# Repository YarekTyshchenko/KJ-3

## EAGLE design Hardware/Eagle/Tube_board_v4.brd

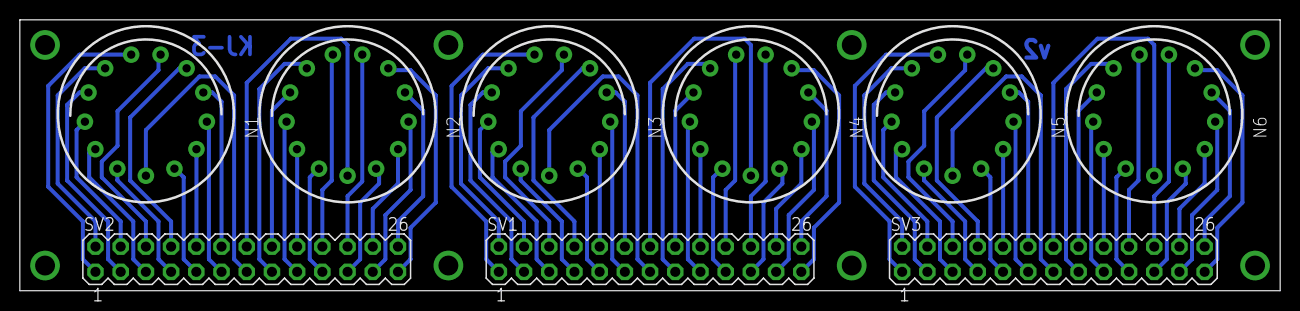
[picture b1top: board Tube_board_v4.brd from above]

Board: 2 copper layers, 127.0 x 27.3 mm, 9 parts (0 on the bottom side), 9 nets.

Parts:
N1, N2, N3, N4, N5, N6: IN-14
SV1, SV2, SV3: MA13-2

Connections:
unnamed: N1.A, SV2.13
unnamed: N2.A, SV2.14
unnamed: N1.0, N1.1, N1.2, N1.3, N1.4, N1.5, N1.6, N1.7, N1.8, N1.9, N1.LHDP, N1.RHDP, N2.0, N2.1, N2.2, N2.3, N2.4, N2.5, N2.6, N2.7, N2.8, N2.9, N2.LHDP, N2.RHDP, SV2.1, SV2.2, SV2.3, SV2.4, SV2.5, SV2.6, SV2.7, SV2.8, SV2.9, SV2.10, SV2.11, SV2.12, SV2.15, SV2.16, SV2.17, SV2.18, SV2.19, SV2.20, SV2.21, SV2.22, SV2.23, SV2.24, SV2.25, SV2.26
unnamed: N3.A, SV1.13
unnamed: N4.A, SV1.14
unnamed: N3.0, N3.1, N3.2, N3.3, N3.4, N3.5, N3.6, N3.7, N3.8, N3.9, N3.LHDP, N3.RHDP, N4.0, N4.1, N4.2, N4.3, N4.4, N4.5, N4.6, N4.7, N4.8, N4.9, N4.LHDP, N4.RHDP, SV1.1, SV1.2, SV1.3, SV1.4, SV1.5, SV1.6, SV1.7, SV1.8, SV1.9, SV1.10, SV1.11, SV1.12, SV1.15, SV1.16, SV1.17, SV1.18, SV1.19, SV1.20, SV1.21, SV1.22, SV1.23, SV1.24, SV1.25, SV1.26
unnamed: N5.A, SV3.13
unnamed: N6.A, SV3.14
unnamed: N5.0, N5.1, N5.2, N5.3, N5.4, N5.5, N5.6, N5.7, N5.8, N5.9, N5.LHDP, N5.RHDP, N6.0, N6.1, N6.2, N6.3, N6.4, N6.5, N6.6, N6.7, N6.8, N6.9, N6.LHDP, N6.RHDP, SV3.1, SV3.2, SV3.3, SV3.4, SV3.5, SV3.6, SV3.7, SV3.8, SV3.9, SV3.10, SV3.11, SV3.12, SV3.15, SV3.16, SV3.17, SV3.18, SV3.19, SV3.20, SV3.21, SV3.22, SV3.23, SV3.24, SV3.25, SV3.26

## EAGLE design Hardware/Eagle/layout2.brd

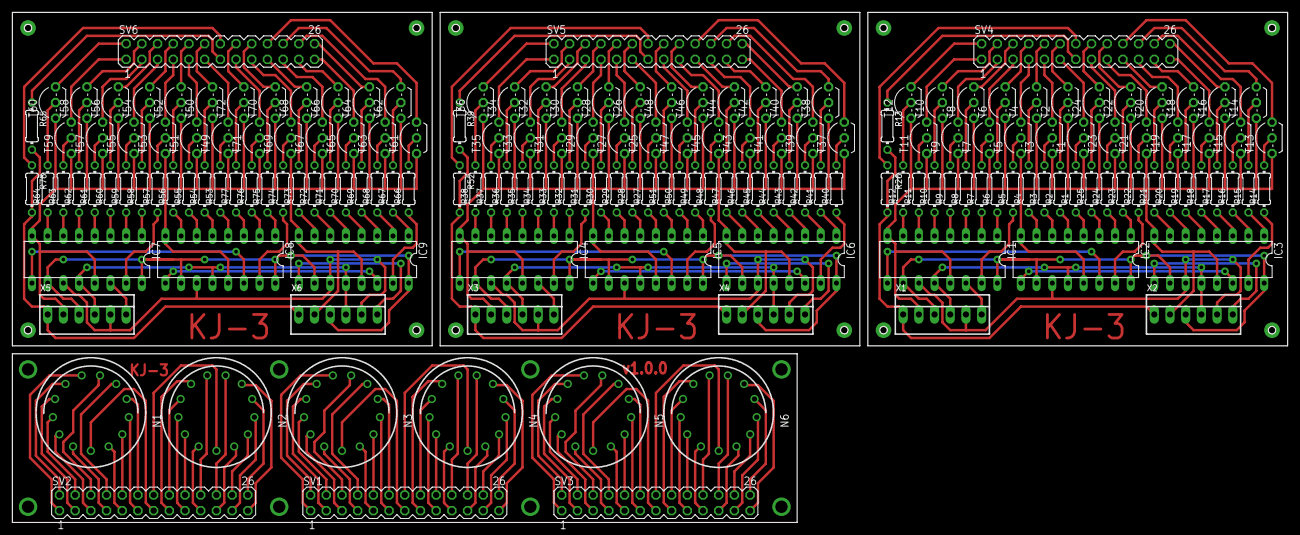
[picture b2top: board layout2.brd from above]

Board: 2 copper layers, 206.4 x 82.5 mm, 177 parts (0 on the bottom side), 258 nets.

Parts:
IC1, IC2, IC3, IC4, IC5, IC6, IC7, IC8, IC9: 74LS595N; DIL16
N1, N2, N3, N4, N5, N6: IN-14
R1, R2, R3, R4, R5, R6, R7, R8, R9, R10, R11, R12, R13, R14, R15, R16, R17, R18, R19, R20, R21, R22, R23, R24, R25, R26, R27, R28, R29, R30, R31, R32, R33, R34, R35, R36, R37, R38, R39, R40, R41, R42, R43, R44, R45, R46, R47, R48, R49, R50, R51, R52, R53, R54, R55, R56, R57, R58, R59, R60, R61, R62, R63, R64, R65, R66, R67, R68, R69, R70, R71, R72, R73, R74, R75, R76, R77, R78: 0204/7
SV1, SV2, SV3, SV4, SV5, SV6: MA13-2
T1, T2, T3, T4, T5, T6, T7, T8, T9, T10, T11, T12, T13, T14, T15, T16, T17, T18, T19, T20, T21, T22, T23, T24, T25, T26, T27, T28, T29, T30, T31, T32, T33, T34, T35, T36, T37, T38, T39, T40, T41, T42, T43, T44, T45, T46, T47, T48, T49, T50, T51, T52, T53, T54, T55, T56, T57, T58, T59, T60, T61, T62, T63, T64, T65, T66, T67, T68, T69, T70, T71, T72: TO92-EBC
X1, X2, X3, X4, X5, X6: 22-23-2061

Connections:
GND: IC1.8, IC1.13, IC2.8, IC2.13, IC3.8, IC3.13, T1.E, T2.E, T3.E, T4.E, T5.E, T6.E, T7.E, T8.E, T9.E, T10.E, T11.E, T12.E, T13.E, T14.E, T15.E, T16.E, T17.E, T18.E, T19.E, T20.E, T21.E, T22.E, T23.E, T24.E, X1.2, X2.2
GND1: IC4.8, IC4.13, IC5.8, IC5.13, IC6.8, IC6.13, T25.E, T26.E, T27.E, T28.E, T29.E, T30.E, T31.E, T32.E, T33.E, T34.E, T35.E, T36.E, T37.E, T38.E, T39.E, T40.E, T41.E, T42.E, T43.E, T44.E, T45.E, T46.E, T47.E, T48.E, X3.2, X4.2
GND2: IC7.8, IC7.13, IC8.8, IC8.13, IC9.8, IC9.13, T49.E, T50.E, T51.E, T52.E, T53.E, T54.E, T55.E, T56.E, T57.E, T58.E, T59.E, T60.E, T61.E, T62.E, T63.E, T64.E, T65.E, T66.E, T67.E, T68.E, T69.E, T70.E, T71.E, T72.E, X5.2, X6.2
unnamed: N1.A, SV2.13
unnamed: N2.A, SV2.14
unnamed: N1.0, N1.1, N1.2, N1.3, N1.4, N1.5, N1.6, N1.7, N1.8, N1.9, N1.LHDP, N1.RHDP, N2.0, N2.1, N2.2, N2.3, N2.4, N2.5, N2.6, N2.7, N2.8, N2.9, N2.LHDP, N2.RHDP, SV2.1, SV2.2, SV2.3, SV2.4, SV2.5, SV2.6, SV2.7, SV2.8, SV2.9, SV2.10, SV2.11, SV2.12, SV2.15, SV2.16, SV2.17, SV2.18, SV2.19, SV2.20, SV2.21, SV2.22, SV2.23, SV2.24, SV2.25, SV2.26
unnamed: N3.A, SV1.13
unnamed: N4.A, SV1.14
unnamed: N3.0, N3.1, N3.2, N3.3, N3.4, N3.5, N3.6, N3.7, N3.8, N3.9, N3.LHDP, N3.RHDP, N4.0, N4.1, N4.2, N4.3, N4.4, N4.5, N4.6, N4.7, N4.8, N4.9, N4.LHDP, N4.RHDP, SV1.1, SV1.2, SV1.3, SV1.4, SV1.5, SV1.6, SV1.7, SV1.8, SV1.9, SV1.10, SV1.11, SV1.12, SV1.15, SV1.16, SV1.17, SV1.18, SV1.19, SV1.20, SV1.21, SV1.22, SV1.23, SV1.24, SV1.25, SV1.26
unnamed: N5.A, SV3.13
unnamed: N6.A, SV3.14
unnamed: N5.0, N5.1, N5.2, N5.3, N5.4, N5.5, N5.6, N5.7, N5.8, N5.9, N5.LHDP, N5.RHDP, N6.0, N6.1, N6.2, N6.3, N6.4, N6.5, N6.6, N6.7, N6.8, N6.9, N6.LHDP, N6.RHDP, SV3.1, SV3.2, SV3.3, SV3.4, SV3.5, SV3.6, SV3.7, SV3.8, SV3.9, SV3.10, SV3.11, SV3.12, SV3.15, SV3.16, SV3.17, SV3.18, SV3.19, SV3.20, SV3.21, SV3.22, SV3.23, SV3.24, SV3.25, SV3.26
unnamed: R12.2, T12.B
unnamed: R11.2, T11.B
unnamed: R10.2, T10.B
unnamed: R9.2, T9.B
unnamed: R8.2, T8.B
unnamed: R7.2, T7.B
unnamed: R6.2, T6.B
unnamed: R5.2, T5.B
unnamed: R4.2, T4.B
unnamed: R3.2, T3.B
unnamed: R2.2, T2.B
unnamed: R1.2, T1.B
unnamed: SV4.3, T9.C
unnamed: SV4.6, T8.C
unnamed: SV4.5, T7.C
unnamed: SV4.12, T2.C
unnamed: SV4.9, T3.C
unnamed: SV4.8, T6.C
unnamed: SV4.7, T5.C
unnamed: SV4.10, T4.C
unnamed: R25.2, T24.B
unnamed: R24.2, T23.B
unnamed: R23.2, T22.B
unnamed: R22.2, T21.B
unnamed: R21.2, T20.B
unnamed: R20.2, T19.B
unnamed: R19.2, T18.B
unnamed: R18.2, T17.B
unnamed: R17.2, T16.B
unnamed: R16.2, T15.B
unnamed: R15.2, T14.B
unnamed: R14.2, T13.B
unnamed: SV4.16, T24.C
unnamed: SV4.15, T23.C
unnamed: SV4.18, T22.C
unnamed: SV4.17, T21.C
unnamed: SV4.19, T20.C
unnamed: SV4.21, T19.C
unnamed: SV4.20, T13.C
unnamed: SV4.22, T14.C
unnamed: SV4.24, T15.C
unnamed: SV4.23, T18.C
unnamed: SV4.25, T17.C
unnamed: SV4.26, T16.C
unnamed: R13.2, R26.2, X1.1, X2.1
unnamed: IC1.9, IC2.14
unnamed: IC2.9, IC3.14
unnamed: IC3.9, X2.6
unnamed: IC1.14, X1.6
unnamed: IC1.11, IC2.11, IC3.11, X1.5, X2.5
unnamed: IC1.12, IC2.12, IC3.12, X1.4, X2.4
unnamed: SV4.11, T1.C
unnamed: R26.1, SV4.14
unnamed: R13.1, SV4.13
unnamed: SV4.2, T12.C
unnamed: SV4.1, T11.C
unnamed: SV4.4, T10.C
unnamed: IC1.7, R12.1
unnamed: IC1.6, R11.1
unnamed: IC1.5, R10.1
unnamed: IC1.4, R9.1
unnamed: IC1.3, R8.1
unnamed: IC1.2, R7.1
unnamed: IC1.1, R6.1
unnamed: IC1.15, R5.1
unnamed: IC2.7, R4.1
unnamed: IC2.6, R3.1
unnamed: IC2.5, R2.1
unnamed: IC2.4, R1.1
unnamed: IC2.3, R25.1
unnamed: IC2.2, R24.1
unnamed: IC2.1, R23.1
unnamed: IC2.15, R22.1
unnamed: IC3.7, R21.1
unnamed: IC3.6, R20.1
unnamed: IC3.5, R19.1
unnamed: IC3.4, R18.1
unnamed: IC3.3, R17.1
unnamed: IC3.2, R16.1
unnamed: IC3.1, R15.1
unnamed: IC3.15, R14.1
unnamed: R38.2, T36.B
unnamed: R37.2, T35.B
unnamed: R36.2, T34.B
unnamed: R35.2, T33.B
unnamed: R34.2, T32.B
unnamed: R33.2, T31.B
unnamed: R32.2, T30.B
unnamed: R31.2, T29.B
unnamed: R30.2, T28.B
unnamed: R29.2, T27.B
unnamed: R28.2, T26.B
unnamed: R27.2, T25.B
unnamed: SV5.3, T33.C
unnamed: SV5.6, T32.C
unnamed: SV5.5, T31.C
unnamed: SV5.12, T26.C
unnamed: SV5.9, T27.C
unnamed: SV5.8, T30.C
unnamed: SV5.7, T29.C
unnamed: SV5.10, T28.C
unnamed: R51.2, T48.B
unnamed: R50.2, T47.B
unnamed: R49.2, T46.B
unnamed: R48.2, T45.B
unnamed: R47.2, T44.B
unnamed: R46.2, T43.B
unnamed: R45.2, T42.B
unnamed: R44.2, T41.B
unnamed: R43.2, T40.B
unnamed: R42.2, T39.B
unnamed: R41.2, T38.B
unnamed: R40.2, T37.B
unnamed: SV5.16, T48.C
unnamed: SV5.15, T47.C
unnamed: SV5.18, T46.C
unnamed: SV5.17, T45.C
unnamed: SV5.19, T44.C
unnamed: SV5.21, T43.C
unnamed: SV5.20, T37.C
unnamed: SV5.22, T38.C
unnamed: SV5.24, T39.C
unnamed: SV5.23, T42.C
unnamed: SV5.25, T41.C
unnamed: SV5.26, T40.C
unnamed: IC4.7, R38.1
unnamed: IC4.6, R37.1
unnamed: IC4.5, R36.1
unnamed: IC4.4, R35.1
unnamed: IC4.3, R34.1
unnamed: IC4.2, R33.1
unnamed: IC4.1, R32.1
unnamed: IC4.15, R31.1
unnamed: IC5.7, R30.1
unnamed: IC5.6, R29.1
unnamed: IC5.5, R28.1
unnamed: IC5.4, R27.1
unnamed: IC5.3, R51.1
unnamed: IC5.2, R50.1
unnamed: IC5.1, R49.1
unnamed: IC5.15, R48.1
unnamed: IC6.7, R47.1
unnamed: IC6.6, R46.1
unnamed: IC6.5, R45.1
unnamed: IC6.4, R44.1
unnamed: IC6.3, R43.1
unnamed: IC6.2, R42.1
unnamed: IC6.1, R41.1
unnamed: IC6.15, R40.1
unnamed: R39.2, R52.2, X3.1, X4.1
unnamed: IC4.9, IC5.14
unnamed: IC5.9, IC6.14
unnamed: IC6.9, X4.6
unnamed: IC4.14, X3.6
unnamed: IC4.11, IC5.11, IC6.11, X3.5, X4.5
unnamed: IC4.12, IC5.12, IC6.12, X3.4, X4.4
unnamed: SV5.11, T25.C
unnamed: R52.1, SV5.14
unnamed: R39.1, SV5.13
unnamed: SV5.2, T36.C
unnamed: SV5.1, T35.C
unnamed: SV5.4, T34.C
unnamed: R64.2, T60.B
unnamed: R63.2, T59.B
unnamed: R62.2, T58.B
unnamed: R61.2, T57.B
unnamed: R60.2, T56.B
unnamed: R59.2, T55.B
unnamed: R58.2, T54.B
unnamed: R57.2, T53.B
unnamed: R56.2, T52.B
unnamed: R55.2, T51.B
unnamed: R54.2, T50.B
unnamed: R53.2, T49.B
unnamed: SV6.3, T57.C
unnamed: SV6.6, T56.C
unnamed: SV6.5, T55.C
unnamed: SV6.12, T50.C
unnamed: SV6.9, T51.C
unnamed: SV6.8, T54.C
unnamed: SV6.7, T53.C
unnamed: SV6.10, T52.C
unnamed: R77.2, T72.B
unnamed: R76.2, T71.B
unnamed: R75.2, T70.B
unnamed: R74.2, T69.B
unnamed: R73.2, T68.B
unnamed: R72.2, T67.B
unnamed: R71.2, T66.B
unnamed: R70.2, T65.B
unnamed: R69.2, T64.B
unnamed: R68.2, T63.B
unnamed: R67.2, T62.B
unnamed: R66.2, T61.B
unnamed: SV6.16, T72.C
unnamed: SV6.15, T71.C
unnamed: SV6.18, T70.C
unnamed: SV6.17, T69.C
unnamed: SV6.19, T68.C
unnamed: SV6.21, T67.C
unnamed: SV6.20, T61.C
unnamed: SV6.22, T62.C
unnamed: SV6.24, T63.C
unnamed: SV6.23, T66.C
unnamed: SV6.25, T65.C
unnamed: SV6.26, T64.C
unnamed: IC7.7, R64.1
unnamed: IC7.6, R63.1
unnamed: IC7.5, R62.1
unnamed: IC7.4, R61.1
unnamed: IC7.3, R60.1
unnamed: IC7.2, R59.1
unnamed: IC7.1, R58.1
unnamed: IC7.15, R57.1
unnamed: IC8.7, R56.1
unnamed: IC8.6, R55.1
unnamed: IC8.5, R54.1
unnamed: IC8.4, R53.1
unnamed: IC8.3, R77.1
unnamed: IC8.2, R76.1
unnamed: IC8.1, R75.1
unnamed: IC8.15, R74.1
unnamed: IC9.7, R73.1
unnamed: IC9.6, R72.1
unnamed: IC9.5, R71.1
unnamed: IC9.4, R70.1
unnamed: IC9.3, R69.1
unnamed: IC9.2, R68.1
unnamed: IC9.1, R67.1
unnamed: IC9.15, R66.1
unnamed: R65.2, R78.2, X5.1, X6.1
unnamed: IC7.9, IC8.14
unnamed: IC8.9, IC9.14
unnamed: IC9.9, X6.6
unnamed: IC7.14, X5.6
unnamed: IC7.11, IC8.11, IC9.11, X5.5, X6.5
unnamed: IC7.12, IC8.12, IC9.12, X5.4, X6.4
unnamed: SV6.11, T49.C
unnamed: R78.1, SV6.14
unnamed: R65.1, SV6.13
unnamed: SV6.2, T60.C
unnamed: SV6.1, T59.C
unnamed: SV6.4, T58.C
VCC: IC1.10, IC1.16, IC2.10, IC2.16, IC3.10, IC3.16, X1.3, X2.3
VCC1: IC4.10, IC4.16, IC5.10, IC5.16, IC6.10, IC6.16, X3.3, X4.3
VCC2: IC7.10, IC7.16, IC8.10, IC8.16, IC9.10, IC9.16, X5.3, X6.3

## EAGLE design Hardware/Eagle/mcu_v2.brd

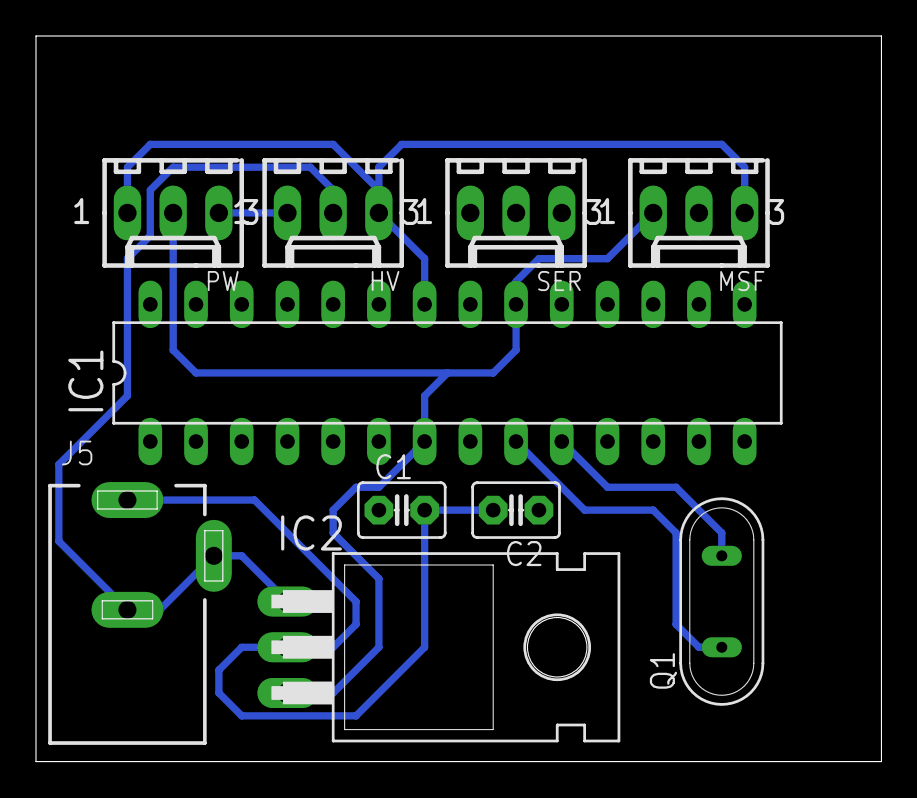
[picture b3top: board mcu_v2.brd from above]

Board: 2 copper layers, 47.0 x 40.3 mm, 10 parts (0 on the bottom side), 10 nets.

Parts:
C1, C2: C2.5-3
HV: 22-27-2031-03; 6410-03
IC1: MEGA8-P; DIL28-3
IC2: 7805T; TO220H
J5: DCJ0202
MSF: 22-27-2031-03; 6410-03
PW: 22-27-2031-03; 6410-03
Q1: QS
SER: 22-27-2031-03; 6410-03

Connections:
GND: C1.2, C2.2, HV.3, IC1.8, IC1.22, IC2.2, J5.1, MSF.3, PW.1
unnamed: HV.2, IC2.1, J5.2, J5.3
unnamed: HV.1, PW.3
unnamed: C2.1, IC1.10, Q1.2
unnamed: C1.1, IC1.9, Q1.1
unnamed: IC1.5, MSF.2
unnamed: IC1.23, SER.1
unnamed: IC1.24, SER.2
unnamed: IC1.25, SER.3
VCC: IC1.7, IC1.20, IC2.3, MSF.1, PW.2
